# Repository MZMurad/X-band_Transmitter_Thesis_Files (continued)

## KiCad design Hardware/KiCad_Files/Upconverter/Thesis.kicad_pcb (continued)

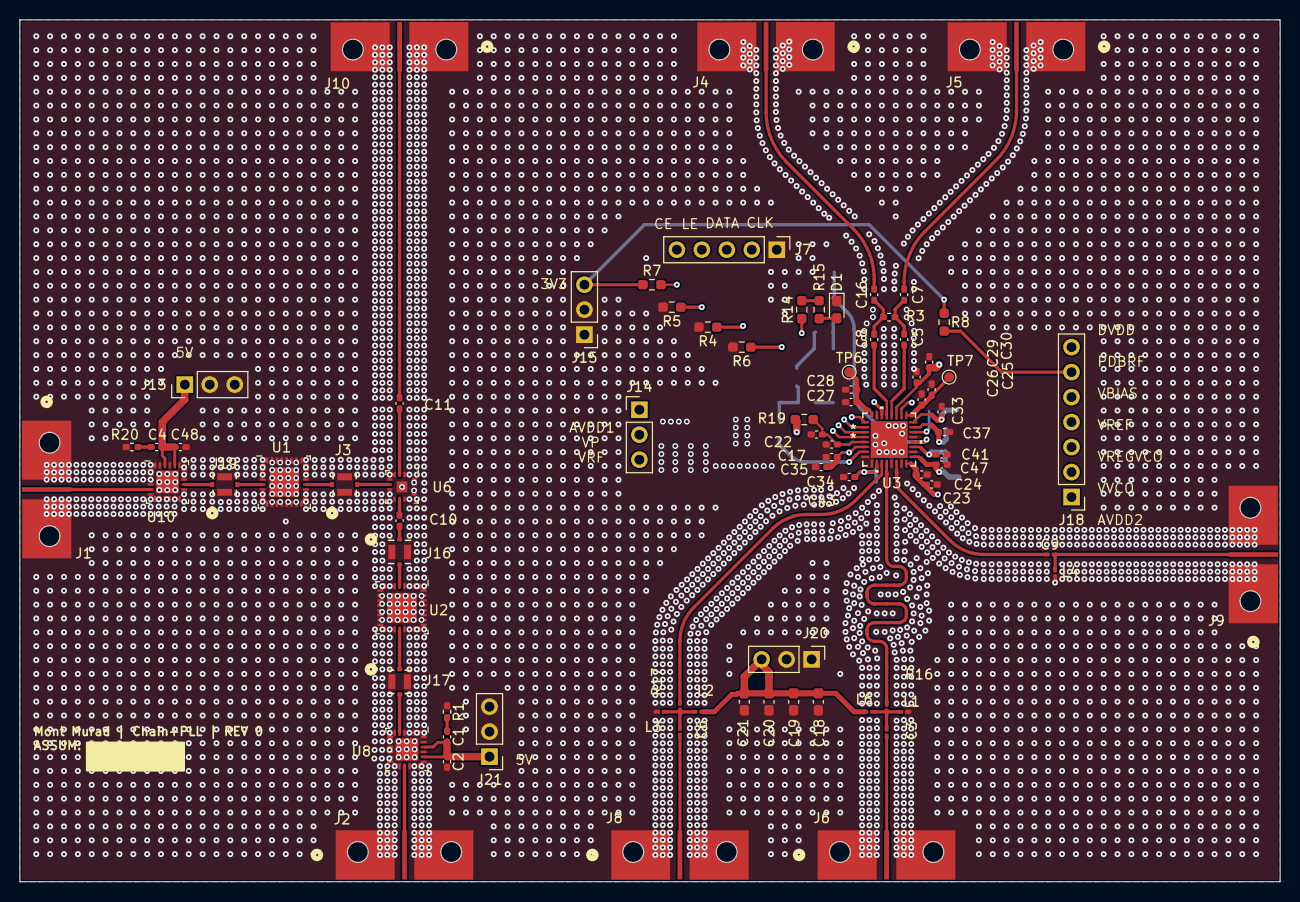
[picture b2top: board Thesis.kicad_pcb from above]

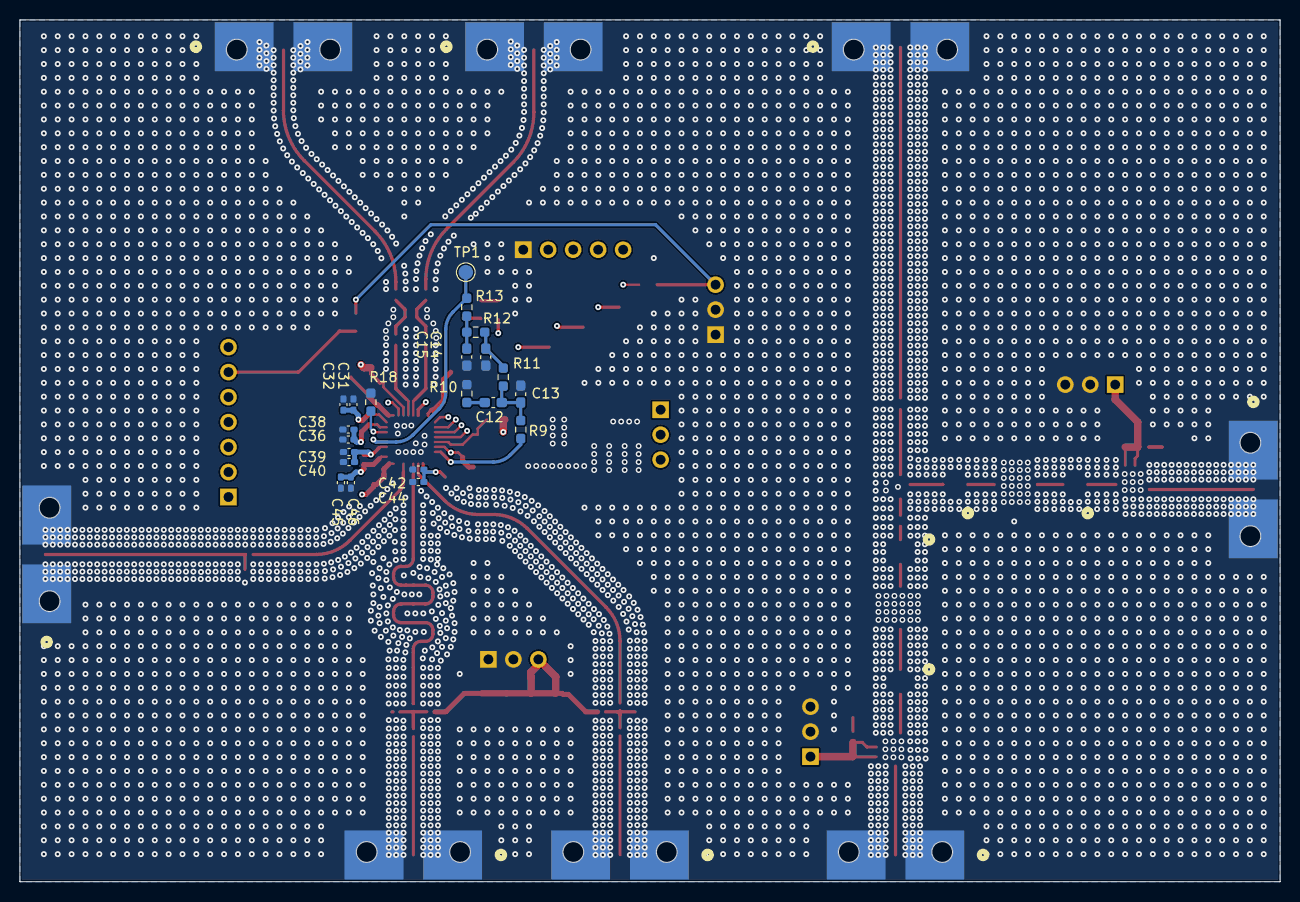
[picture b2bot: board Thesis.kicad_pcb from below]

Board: 4 copper layers, 128.1 x 87.6 mm, 101 parts (21 on the bottom side), 61 nets.

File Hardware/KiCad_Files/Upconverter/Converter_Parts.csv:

"Value","Reference","Datasheet","Footprint","Qty","DNP"
"0.1u","C1,C2,C4,C17,C23,C25,C27,C29,C31,C34,C48","~","Capacitor_SMD:C_0402_1005Metric_Pad0.74x0.62mm_HandSolder","11",""
"10p","C3,C6,C9","~","Capacitor_SMD:C_0201_0603Metric_Pad0.64x0.40mm_HandSolder","3",""
"1000p","C5,C7,C8,C16,C37,C40,C43,C46","~","Capacitor_SMD:C_0402_1005Metric_Pad0.74x0.62mm_HandSolder","8",""
"2p","C10,C11","~","Capacitor_SMD:C_0402_1005Metric_Pad0.74x0.62mm_HandSolder","2",""
"0.47u","C12","~","Capacitor_SMD:C_0603_1608Metric_Pad1.08x0.95mm_HandSolder","1",""
"22n","C13","~","Capacitor_SMD:C_0603_1608Metric_Pad1.08x0.95mm_HandSolder","1",""
"1000p","C14","~","Capacitor_SMD:C_0603_1608Metric_Pad1.08x0.95mm_HandSolder","1",""
"10p","C15","~","Capacitor_SMD:C_0603_1608Metric_Pad1.08x0.95mm_HandSolder","1",""
"120p","C18,C21","~","Capacitor_SMD:C_0603_1608Metric_Pad1.08x0.95mm_HandSolder","2",""
"1u","C19","~","Capacitor_SMD:C_0603_1608Metric_Pad1.08x0.95mm_HandSolder","1",""
"0.1u","C20","~","Capacitor_SMD:C_0603_1608Metric_Pad1.08x0.95mm_HandSolder","1",""
"10p","C22,C24,C26,C28,C30,C32,C35,C38,C39,C42,C45","~","Capacitor_SMD:C_0402_1005Metric_Pad0.74x0.62mm_HandSolder","11",""
"DNP(1u)","C33","~","Capacitor_SMD:C_0402_1005Metric_Pad0.74x0.62mm_HandSolder","1",""
"4.7u","C36","~","Capacitor_SMD:C_0402_1005Metric_Pad0.74x0.62mm_HandSolder","1",""
"10u","C41","~","Capacitor_SMD:C_0402_1005Metric_Pad0.74x0.62mm_HandSolder","1",""
"1u","C44,C47","~","Capacitor_SMD:C_0402_1005Metric_Pad0.74x0.62mm_HandSolder","2",""
"LED","D1","~","LED_SMD:LED_0603_1608Metric_Pad1.05x0.95mm_HandSolder","1",""
"32K243-40ML5","J1,J2,J4,J5,J6,J8,J9,J10","32K243-40ML5","32K243-40ML5:CONN_32K243-40ML5_RBG","8",""
"MM8030-2610RK0","J3,J16,J17,J19","MM8030-2610RK0","MM8030_2610RJ3:MM8030-2610RK0_MUR","4",""
"Conn_01x05_Pin","J7","~","Connector_PinHeader_2.54mm:PinHeader_1x05_P2.54mm_Vertical","1",""
"Conn_01x03_Pin","J13,J14,J15,J20,J21","~","Connector_PinHeader_2.54mm:PinHeader_1x03_P2.54mm_Vertical","5",""
"Conn_01x07_Pin","J18","~","Connector_PinHeader_2.54mm:PinHeader_1x07_P2.54mm_Vertical","1",""
"DNP(4.7n)","L1,L3,L4","~","Inductor_SMD:L_0201_0603Metric_Pad0.64x0.40mm_HandSolder","3",""
"7.4n","L2,L6","~","Inductor_SMD:L_0201_0603Metric_Pad0.64x0.40mm_HandSolder","2",""
"10R","R1,R20","~","Resistor_SMD:R_0402_1005Metric_Pad0.72x0.64mm_HandSolder","2",""
"100R","R3","~","Resistor_SMD:R_0402_1005Metric_Pad0.72x0.64mm_HandSolder","1",""
"1.8k","R4,R5,R6","~","Resistor_SMD:R_0603_1608Metric_Pad0.98x0.95mm_HandSolder","3",""
"1.5k","R7","~","Resistor_SMD:R_0603_1608Metric_Pad0.98x0.95mm_HandSolder","1",""
"10k","R8","~","Resistor_SMD:R_0603_1608Metric_Pad0.98x0.95mm_HandSolder","1",""
"0R","R9,R12,R13,R14,R19","~","Resistor_SMD:R_0603_1608Metric_Pad0.98x0.95mm_HandSolder","5",""
"220","R10","~","Resistor_SMD:R_0603_1608Metric_Pad0.98x0.95mm_HandSolder","1",""
"470R","R11","~","Resistor_SMD:R_0603_1608Metric_Pad0.98x0.95mm_HandSolder","1",""
"68R","R15","~","Resistor_SMD:R_0603_1608Metric_Pad0.98x0.95mm_HandSolder","1",""
"0R","R16,R17","~","Resistor_SMD:R_0201_0603Metric_Pad0.64x0.40mm_HandSolder","2",""
"5.1k","R18","~","Resistor_SMD:R_0603_1608Metric_Pad0.98x0.95mm_HandSolder","1",""
"TestPoint","TP1","~","TestPoint:TestPoint_Pad_D1.5mm","1",""
"TestPoint","TP6,TP7","~","TestPoint:TestPoint_Pad_D1.0mm","2",""
"MFBP-00094PSM","U1","","Thesis_Marki:QFN-32_EP_5x5_Pitch0.5mm","1",""
"MFBA-00004PSM","U2","","Thesis_Marki:QFN-32_EP_5x5_Pitch0.5mm","1",""
"ADF5355BCPZ","U3","https://www.analog.com/media/en/technical-documentation/data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","ADF5355BCPZ:CP-32-12_ADI","1",""
"MM1-0222LSM-2","U6","","Thesis_Marki:QFN-16_EP_3x3_Pitch0.5mm","1",""
"APM-7516PSM","U8,U10","","Thesis_Marki:QFN-24_EP_4x4_Pitch0.5mm","2",""

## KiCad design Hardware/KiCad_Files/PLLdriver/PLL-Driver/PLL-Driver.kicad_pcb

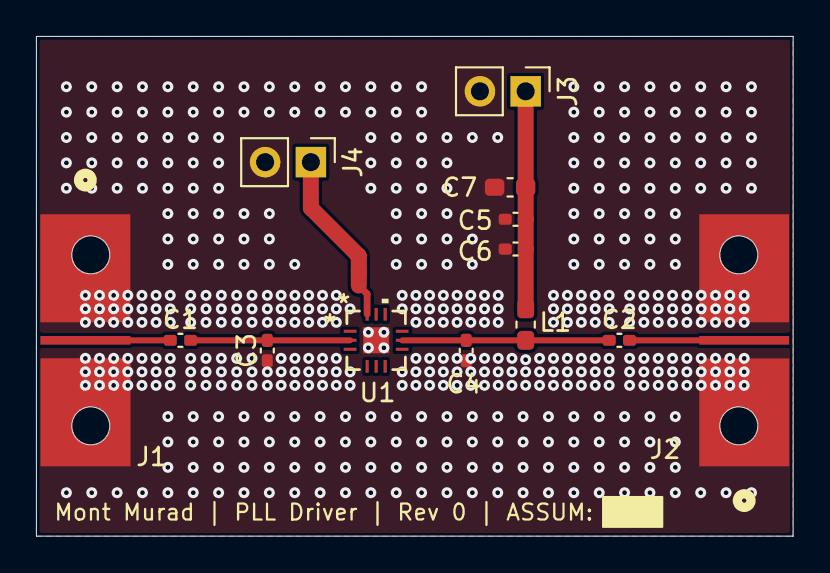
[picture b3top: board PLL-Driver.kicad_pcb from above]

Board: 4 copper layers, 42.0 x 27.8 mm, 13 parts (0 on the bottom side), 7 nets.

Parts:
C1, C2: 100p; C_0402_1005Metric_Pad0.74x0.62mm_HandSolder
C3, C4: 0.3p; C_0402_1005Metric_Pad0.74x0.62mm_HandSolder
C5: 10p; C_0402_1005Metric_Pad0.74x0.62mm_HandSolder
C6: 1u; C_0402_1005Metric_Pad0.74x0.62mm_HandSolder
C7: 10u; C_0603_1608Metric_Pad1.08x0.95mm_HandSolder
J1, J2: 32K243-40ML5; CONN_32K243-40ML5_RBG
J3, J4: Conn_01x02_Pin; PinHeader_1x02_P2.54mm_Vertical
L1: 33nH; L_0603_1608Metric_Pad1.05x0.95mm_HandSolder
U1: PMA3-83MP+; DQ1225_MNC

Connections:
/RFIN: C1.1, J1.1
/RFOUT: C2.2, J2.1
/VDD: C5.2, C6.2, C7.2, J3.1, L1.1
/Vladj: J4.1, U1.12 (ladj)
GND: C3.1, C4.1, C5.1, C6.1, C7.1, J1.2, J1.3, J1.4, J1.5, J2.2, J2.3, J2.4, J2.5, J3.2, J4.2, U1.13 (GND)
unnamed: C1.2, C3.2, U1.2 (RF-IN)
unnamed: C2.1, C4.2, L1.2, U1.8 (RF-OUT/VDD)

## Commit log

2026-05-20 Created File Structure
2026-05-20 testing folder store
2026-05-20 Added KiCad Files
2026-05-20 Added GNU BPSK and updated Read Me
2026-05-21 filled data, python captures, GNU bpsk and qpsk, added readme where needed
2026-05-21 added BOM of comps
2026-06-11 Added QPSK flow graphs and data
2026-06-11 Added readme
